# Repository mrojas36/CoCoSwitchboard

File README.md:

# CoCoSwitchboard
Membrane Replacement for TRS-80 Color Computer Keyboards

## Color Computer 3 Switchboard

## Color Computer 2 Switchboard

## Color Computer 1 Switchboard

## Keyboard Adapter

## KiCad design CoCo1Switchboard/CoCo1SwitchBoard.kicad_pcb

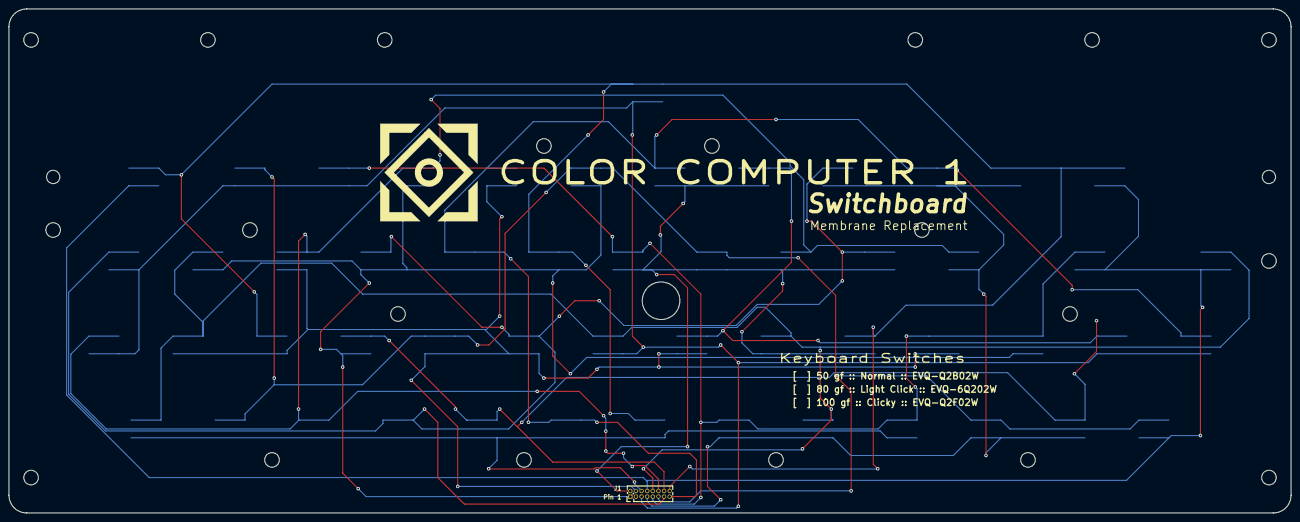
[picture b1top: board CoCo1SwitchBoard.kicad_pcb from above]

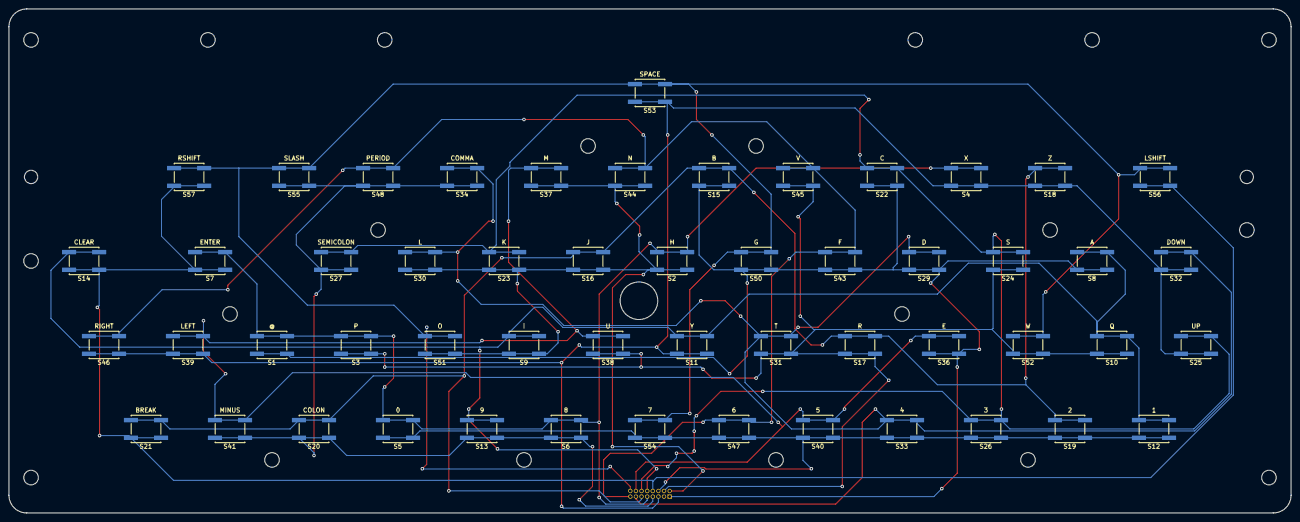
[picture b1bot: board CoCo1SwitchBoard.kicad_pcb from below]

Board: 2 copper layers, 290.0 x 114.0 mm, 54 parts (53 on the bottom side), 15 nets.

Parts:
J1: Conn_01x16; PinHeader_2x08_P1.27mm_Vertical
S1: @; SW_SPST_EVQQ2
S2: H; SW_SPST_EVQQ2
S3: P; SW_SPST_EVQQ2
S4: X; SW_SPST_EVQQ2
S5: 0; SW_SPST_EVQQ2
S6: 8; SW_SPST_EVQQ2
S7: ENTER; SW_SPST_EVQQ2
S8: A; SW_SPST_EVQQ2
S9: I; SW_SPST_EVQQ2
S10: Q; SW_SPST_EVQQ2
S11: Y; SW_SPST_EVQQ2
S12: 1; SW_SPST_EVQQ2
S13: 9; SW_SPST_EVQQ2
S14: CLEAR; SW_SPST_EVQQ2
S15: B; SW_SPST_EVQQ2
S16: J; SW_SPST_EVQQ2
S17: R; SW_SPST_EVQQ2
S18: Z; SW_SPST_EVQQ2
S19: 2; SW_SPST_EVQQ2
S20: COLON; SW_SPST_EVQQ2
S21: BREAK; SW_SPST_EVQQ2
S22: C; SW_SPST_EVQQ2
S23: K; SW_SPST_EVQQ2
S24: S; SW_SPST_EVQQ2
S25: UP; SW_SPST_EVQQ2
S26: 3; SW_SPST_EVQQ2
S27: SEMICOLON; SW_SPST_EVQQ2
S29: D; SW_SPST_EVQQ2
S30: L; SW_SPST_EVQQ2
S31: T; SW_SPST_EVQQ2
S32: DOWN; SW_SPST_EVQQ2
S33: 4; SW_SPST_EVQQ2
S34: COMMA; SW_SPST_EVQQ2
S36: E; SW_SPST_EVQQ2
S37: M; SW_SPST_EVQQ2
S38: U; SW_SPST_EVQQ2
S39: LEFT; SW_SPST_EVQQ2
S40: 5; SW_SPST_EVQQ2
S41: MINUS; SW_SPST_EVQQ2
S43: F; SW_SPST_EVQQ2
S44: N; SW_SPST_EVQQ2
S45: V; SW_SPST_EVQQ2
S46: RIGHT; SW_SPST_EVQQ2
S47: 6; SW_SPST_EVQQ2
S48: PERIOD; SW_SPST_EVQQ2
S50: G; SW_SPST_EVQQ2
S51: O; SW_SPST_EVQQ2
S52: W; SW_SPST_EVQQ2
S53: SPACE; SW_SPST_EVQQ2
S54: 7; SW_SPST_EVQQ2
S55: SLASH; SW_SPST_EVQQ2
S56: LSHIFT; SW_SPST_EVQQ2
S57: RSHIFT; SW_SPST_EVQQ2

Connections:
PA0: J1.1, S1.1, S8.1, S15.1, S22.1, S29.1, S36.1, S43.1, S50.1
PA1: J1.2, S2.1, S9.1, S16.1, S23.1, S30.1, S37.1, S44.1, S51.1
PA2: J1.4, S3.1, S10.1, S17.1, S24.1, S31.1, S38.1, S45.1, S52.1
PA3: J1.5, S4.1, S11.1, S18.1, S25.1, S32.1, S39.1, S46.1, S53.1
PA4: J1.6, S5.1, S12.1, S19.1, S26.1, S33.1, S40.1, S47.1, S54.1
PA5: J1.7, S6.1, S13.1, S20.1, S27.1, S34.1, S41.1, S48.1, S55.1
PA6: J1.8, S7.1, S14.1, S21.1, S56.1, S57.1
PB0: J1.9, S1.2, S2.2, S3.2, S4.2, S5.2, S6.2, S7.2
PB1: J1.10, S8.2, S9.2, S10.2, S11.2, S12.2, S13.2, S14.2
PB2: J1.11, S15.2, S16.2, S17.2, S18.2, S19.2, S20.2, S21.2
PB3: J1.12, S22.2, S23.2, S24.2, S25.2, S26.2, S27.2
PB4: J1.13, S29.2, S30.2, S31.2, S32.2, S33.2, S34.2
PB5: J1.14, S36.2, S37.2, S38.2, S39.2, S40.2, S41.2
PB6: J1.15, S43.2, S44.2, S45.2, S46.2, S47.2, S48.2
PB7: J1.16, S50.2, S51.2, S52.2, S53.2, S54.2, S55.2, S56.2, S57.2

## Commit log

2022-08-15 Added CoCo1 image of board
2022-08-15 Installation Guide edits
2022-09-06 New Spacer Design
2022-09-06 New Spacer Design for CoCo2
2022-09-09 Added New Spacer Errata
2023-02-24 Added Edge Connector and updated Documentation
